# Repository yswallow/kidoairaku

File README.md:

## 輝度哀楽

### 最低限の説明

* Pi PicoもしくはISP1807ピッチ変換基板で動きます
* Pi PicoのGP10/ISP1807のP0.14をHIGHにするとNeoPixelに電源を供給します
* コンスルーは左側に12ピンを、右側に13ピンを、シルクを白く塗っている位置に合わせて使用してください。Pi Picoを使う場合は20ピンも使用可能です。

#### スイッチや1N4148Wダイオードを除いた部品のBOM

| Index | 部品名 | 販売URL |
|----|----|----|
| U1 | Raspberry Pi Pico | https://ssci.to/6900 |
| U1 | ISP1807ピッチ変換基板 | https://ssci.to/6100 |
| U1 | ISP1807ピッチ変換基板(Type-C) | https://ssci.to/6454 |
| F1 | ポリヒューズ 2012 | https://akizukidenshi.com/catalog/g/gP-13955/ |
| Q1 | Pch パワーMOSFET IRLML6402 | https://akizukidenshi.com/catalog/g/gI-02553/ |
| Q51 | Nch MOSFET 2N7002 | https://akizukidenshi.com/catalog/g/gI-04256/ |
| R1,R51 | 10kΩ抵抗3216 | https://akizukidenshi.com/catalog/g/gR-11802/ |

##### 未実装

J1, D51 "Schot", C51, R52 "400k", R53 "100k"

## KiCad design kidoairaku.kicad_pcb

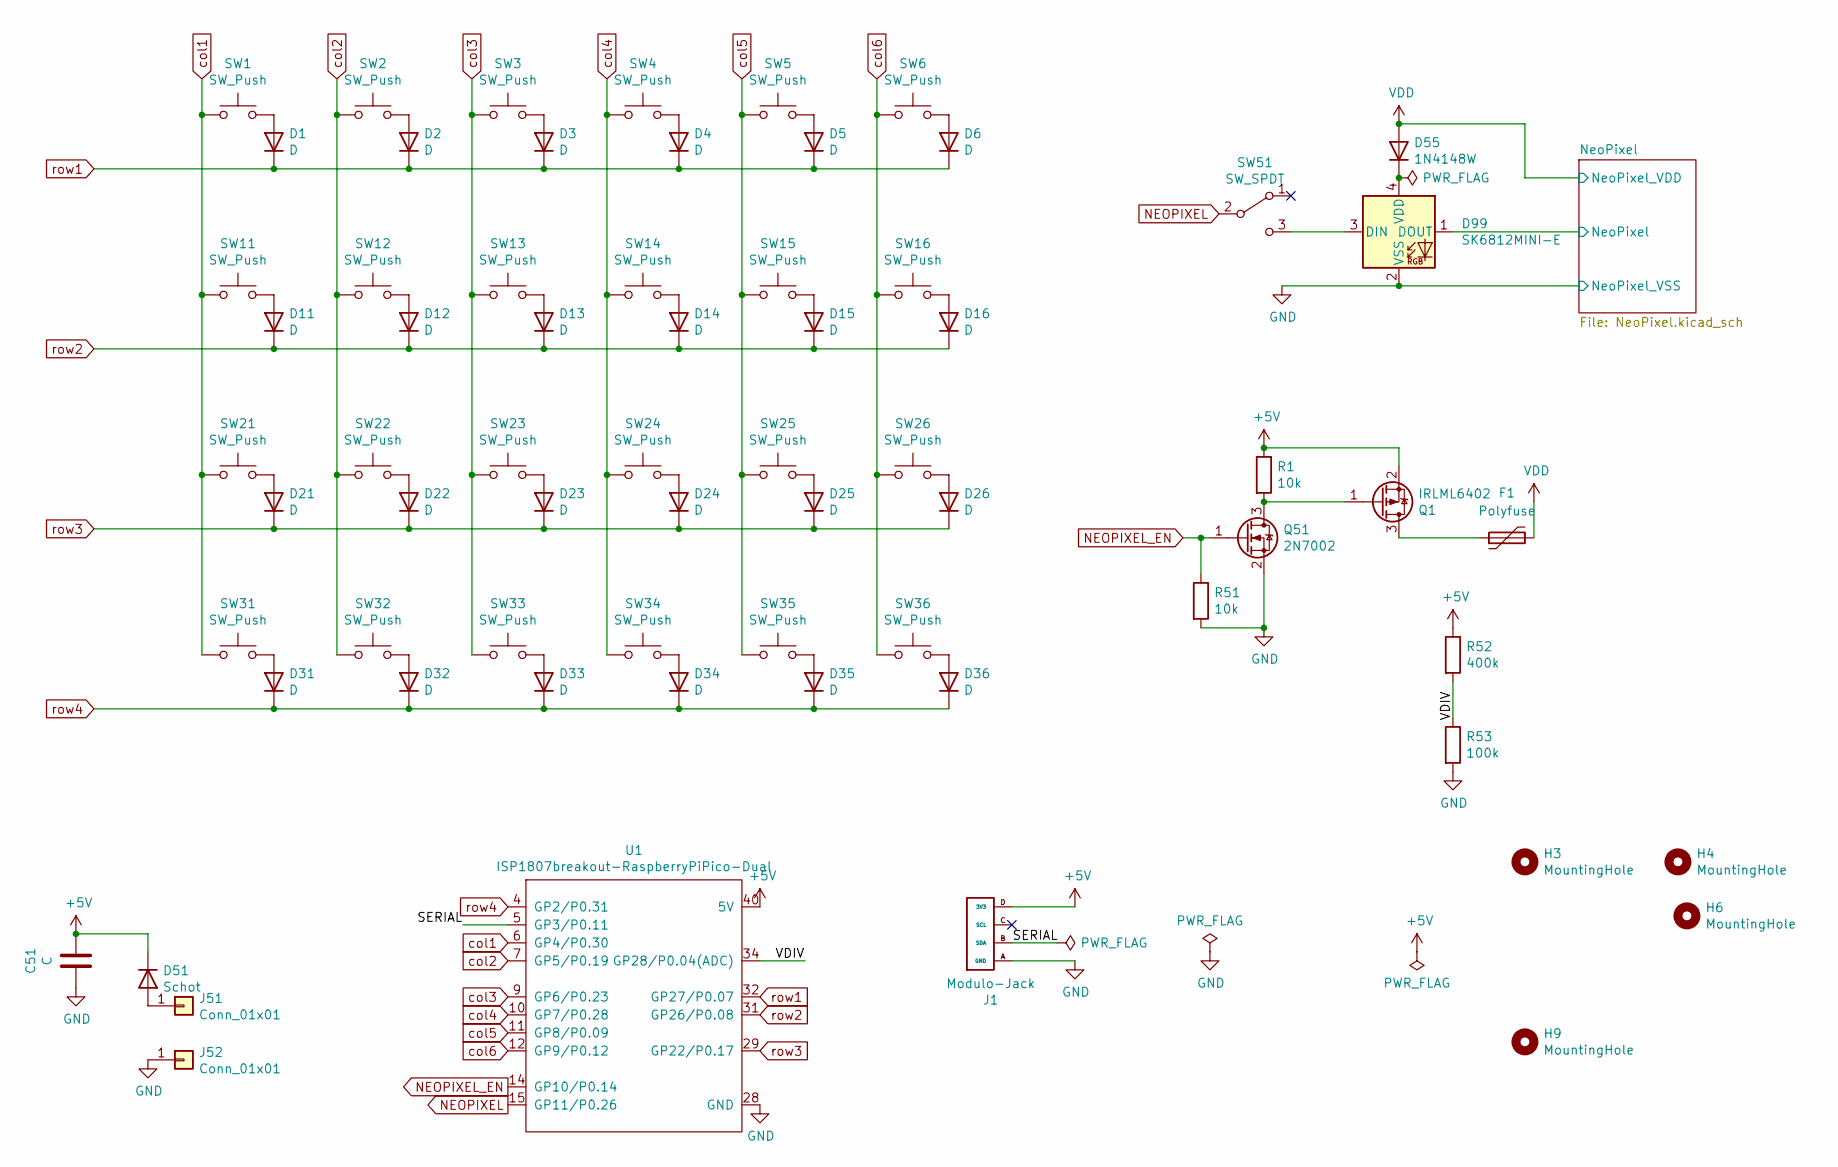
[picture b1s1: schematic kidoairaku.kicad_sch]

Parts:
C51: C; C_1206_3216Metric_Pad1.33x1.80mm_HandSolder
D1, D2, D3, D4, D5, D6, D11, D12, D13, D14, D15, D16, D21, D22, D23, D24, D25, D26, D31, D32, D33, D34, D35, D36: D; D_SOD-123
D51: Schot; D_SOD-123
D55: 1N4148W; D_SOD-123
D99: SK6812MINI-E; SK6812MINI-E_NoSilk-dril
F1: Polyfuse; Fuse_0805_2012Metric_Pad1.15x1.40mm_HandSolder
H3, H4, H6, H9: MountingHole; MountingHole_2.2mm_M2
J1: Modulo-Jack; PJ-320D
J51: Conn_01x01; TestPoint_THTPad_2.0x2.0mm_Drill1.0mm
J52: Conn_01x01; TestPoint_THTPad_D2.0mm_Drill1.0mm
Q1: IRLML6402; SOT-23
Q51: 2N7002; SOT-23
R1, R51: 10k; R_1206_3216Metric_Pad1.30x1.75mm_HandSolder
R52: 400k; R_1206_3216Metric_Pad1.30x1.75mm_HandSolder
R53: 100k; R_1206_3216Metric_Pad1.30x1.75mm_HandSolder
SW1, SW2, SW3, SW4, SW5, SW6, SW11, SW12, SW13, SW14, SW15, SW16, SW21, SW22, SW23, SW24, SW25, SW26, SW31, SW32, SW33, SW34, SW35, SW36: SW_Push; SW_Cherry_MX_1.00u_PCB_Normal
SW51: SW_SPDT; SlideSwitch_SS-12D00
U1: ISP1807breakout-RaspberryPiPico-Dual

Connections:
+5V: C51.1, D51.1 (K), J1.D (3V3), Q1.2 (S), R1.1, R52.1, U1.40 (5V)
/NeoPixel/NeoPixel: D99.1 (DOUT); also elsewhere on the board
/SERIAL: J1.B (SDA), U1.5 (GP3/P0.11)
/VDIV: R52.2, R53.1, U1.34 (GP28/P0.04(ADC))
GND: C51.2, D99.2 (VSS), J1.A (GND), J52.1, Q51.2 (S), R51.2, R53.2, U1.28 (GND); also elsewhere on the board
NEOPIXEL: SW51.2 (B), U1.15 (GP11/P0.26)
NEOPIXEL_EN: Q51.1 (G), R51.1, U1.14 (GP10/P0.14)
unnamed: D1.2 (A), SW1.2
unnamed: D2.2 (A), SW2.2
unnamed: D3.2 (A), SW3.2
unnamed: D4.2 (A), SW4.2
unnamed: D5.2 (A), SW5.2
unnamed: D6.2 (A), SW6.2
unnamed: D11.2 (A), SW11.2
unnamed: D12.2 (A), SW12.2
unnamed: D13.2 (A), SW13.2
unnamed: D14.2 (A), SW14.2
unnamed: D15.2 (A), SW15.2
unnamed: D16.2 (A), SW16.2
unnamed: D21.2 (A), SW21.2
unnamed: D22.2 (A), SW22.2
unnamed: D23.2 (A), SW23.2
unnamed: D24.2 (A), SW24.2
unnamed: D25.2 (A), SW25.2
unnamed: D26.2 (A), SW26.2
unnamed: D31.2 (A), SW31.2
unnamed: D32.2 (A), SW32.2
unnamed: D33.2 (A), SW33.2
unnamed: D34.2 (A), SW34.2
unnamed: D35.2 (A), SW35.2
unnamed: D36.2 (A), SW36.2
unnamed: D51.2 (A), J51.1
unnamed: D55.1 (K), D99.4 (VDD)
unnamed: D99.3 (DIN), SW51.3 (C)
unnamed: F1.1, Q1.3 (D)
unnamed: Q1.1 (G), Q51.3 (D), R1.2
VDD: D55.2 (A), F1.2; also elsewhere on the board
col1: SW1.1, SW11.1, SW21.1, SW31.1, U1.6 (GP4/P0.30)
col2: SW2.1, SW12.1, SW22.1, SW32.1, U1.7 (GP5/P0.19)
col3: SW3.1, SW13.1, SW23.1, SW33.1, U1.9 (GP6/P0.23)
col4: SW4.1, SW14.1, SW24.1, SW34.1, U1.10 (GP7/P0.28)
col5: SW5.1, SW15.1, SW25.1, SW35.1, U1.11 (GP8/P0.09)
col6: SW6.1, SW16.1, SW26.1, SW36.1, U1.12 (GP9/P0.12)
row1: D1.1 (K), D2.1 (K), D3.1 (K), D4.1 (K), D5.1 (K), D6.1 (K), U1.32 (GP27/P0.07)
row2: D11.1 (K), D12.1 (K), D13.1 (K), D14.1 (K), D15.1 (K), D16.1 (K), U1.31 (GP26/P0.08)
row3: D21.1 (K), D22.1 (K), D23.1 (K), D24.1 (K), D25.1 (K), D26.1 (K), U1.29 (GP22/P0.17)
row4: D31.1 (K), D32.1 (K), D33.1 (K), D34.1 (K), D35.1 (K), D36.1 (K), U1.4 (GP2/P0.31)

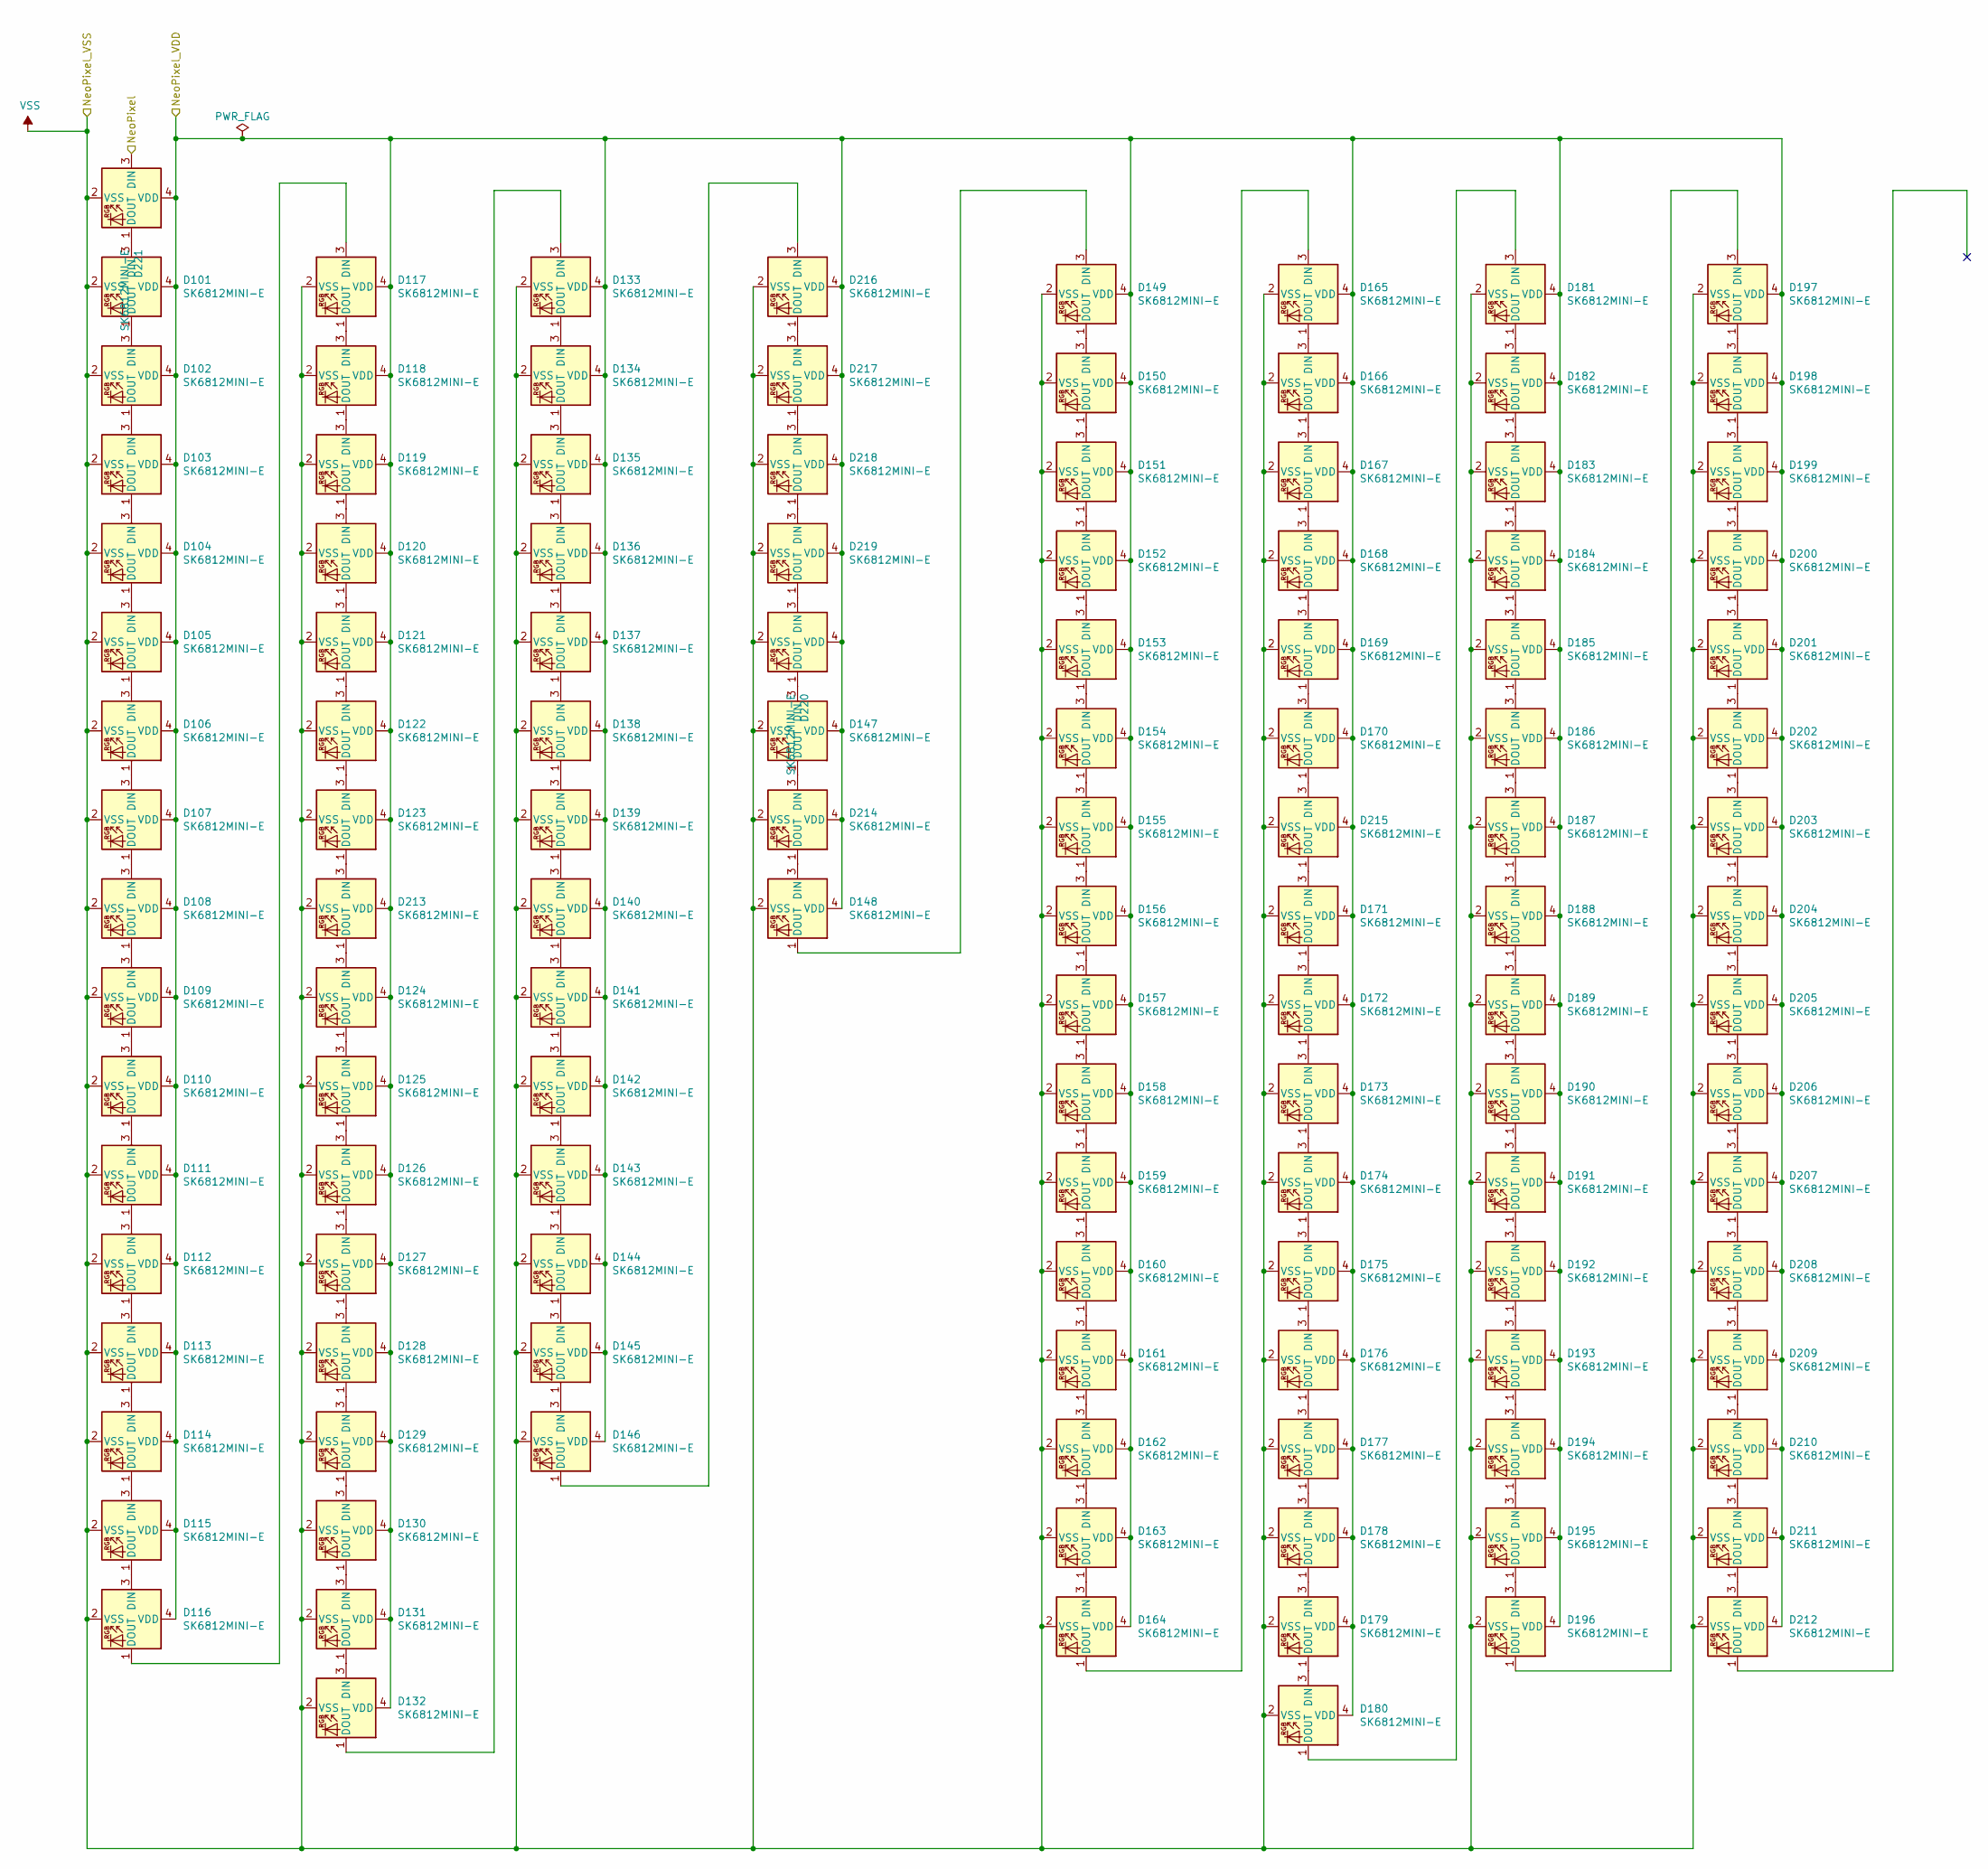
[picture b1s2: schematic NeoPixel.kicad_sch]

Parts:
D101, D102, D103, D104, D105, D106, D107, D108, D109, D110, D111, D112, D113, D114, D115, D116, D117, D118, D119, D120, D121, D122, D123, D124, D125, D126, D127, D128, D129, D130, D131, D132, D133, D134, D135, D136, D137, D138, D139, D140, D141, D142, D143, D144, D145, D146, D147, D148, D149, D150, D151, D152, D153, D154, D155, D156, D157, D158, D159, D160, D161, D162, D163, D164, D165, D166, D167, D168, D169, D170, D171, D172, D173, D174, D175, D176, D177, D178, D179, D180, D181, D182, D183, D184, D185, D186, D187, D188, D189, D190, D191, D192, D213, D214, D215, D216, D217, D218, D219, D220, D221: SK6812MINI-E; SK6812MINI-E_NoSilk-dril
D193, D194, D195, D196, D197, D198, D199, D200, D201, D202, D203, D204, D205, D206, D207, D208, D209, D210, D211, D212: SK6812MINI-E; SK6812MINI-E_NoSilk-dril-front

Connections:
/NeoPixel/NeoPixel: D221.3 (DIN); also elsewhere on the board
GND: D101.2 (VSS), D102.2 (VSS), D103.2 (VSS), D104.2 (VSS), D105.2 (VSS), D106.2 (VSS), D107.2 (VSS), D108.2 (VSS), D109.2 (VSS), D110.2 (VSS), D111.2 (VSS), D112.2 (VSS), D113.2 (VSS), D114.2 (VSS), D115.2 (VSS), D116.2 (VSS), D117.2 (VSS), D118.2 (VSS), D119.2 (VSS), D120.2 (VSS), D121.2 (VSS), D122.2 (VSS), D123.2 (VSS), D124.2 (VSS), D125.2 (VSS), D126.2 (VSS), D127.2 (VSS), D128.2 (VSS), D129.2 (VSS), D130.2 (VSS), D131.2 (VSS), D132.2 (VSS), D133.2 (VSS), D134.2 (VSS), D135.2 (VSS), D136.2 (VSS), D137.2 (VSS), D138.2 (VSS), D139.2 (VSS), D140.2 (VSS), D141.2 (VSS), D142.2 (VSS), D143.2 (VSS), D144.2 (VSS), D145.2 (VSS), D146.2 (VSS), D147.2 (VSS), D148.2 (VSS), D149.2 (VSS), D150.2 (VSS), D151.2 (VSS), D152.2 (VSS), D153.2 (VSS), D154.2 (VSS), D155.2 (VSS), D156.2 (VSS), D157.2 (VSS), D158.2 (VSS), D159.2 (VSS), D160.2 (VSS), D161.2 (VSS), D162.2 (VSS), D163.2 (VSS), D164.2 (VSS), D165.2 (VSS), D166.2 (VSS), D167.2 (VSS), D168.2 (VSS), D169.2 (VSS), D170.2 (VSS), D171.2 (VSS), D172.2 (VSS), D173.2 (VSS), D174.2 (VSS), D175.2 (VSS), D176.2 (VSS), D177.2 (VSS), D178.2 (VSS), D179.2 (VSS), D180.2 (VSS), D181.2 (VSS), D182.2 (VSS), D183.2 (VSS), D184.2 (VSS), D185.2 (VSS), D186.2 (VSS), D187.2 (VSS), D188.2 (VSS), D189.2 (VSS), D190.2 (VSS), D191.2 (VSS), D192.2 (VSS), D193.2 (VSS), D194.2 (VSS), D195.2 (VSS), D196.2 (VSS), D197.2 (VSS), D198.2 (VSS), D199.2 (VSS), D200.2 (VSS), D201.2 (VSS), D202.2 (VSS), D203.2 (VSS), D204.2 (VSS), D205.2 (VSS), D206.2 (VSS), D207.2 (VSS), D208.2 (VSS), D209.2 (VSS), D210.2 (VSS), D211.2 (VSS), D212.2 (VSS), D213.2 (VSS), D214.2 (VSS), D215.2 (VSS), D216.2 (VSS), D217.2 (VSS), D218.2 (VSS), D219.2 (VSS), D220.2 (VSS), D221.2 (VSS); also elsewhere on the board
unnamed: D101.1 (DOUT), D102.3 (DIN)
unnamed: D101.3 (DIN), D221.1 (DOUT)
unnamed: D102.1 (DOUT), D103.3 (DIN)
unnamed: D103.1 (DOUT), D104.3 (DIN)
unnamed: D104.1 (DOUT), D105.3 (DIN)
unnamed: D105.1 (DOUT), D106.3 (DIN)
unnamed: D106.1 (DOUT), D107.3 (DIN)
unnamed: D107.1 (DOUT), D108.3 (DIN)
unnamed: D108.1 (DOUT), D109.3 (DIN)
unnamed: D109.1 (DOUT), D110.3 (DIN)
unnamed: D110.1 (DOUT), D111.3 (DIN)
unnamed: D111.1 (DOUT), D112.3 (DIN)
unnamed: D112.1 (DOUT), D113.3 (DIN)
unnamed: D113.1 (DOUT), D114.3 (DIN)
unnamed: D114.1 (DOUT), D115.3 (DIN)
unnamed: D115.1 (DOUT), D116.3 (DIN)
unnamed: D116.1 (DOUT), D117.3 (DIN)
unnamed: D117.1 (DOUT), D118.3 (DIN)
unnamed: D118.1 (DOUT), D119.3 (DIN)
unnamed: D119.1 (DOUT), D120.3 (DIN)
unnamed: D120.1 (DOUT), D121.3 (DIN)
unnamed: D121.1 (DOUT), D122.3 (DIN)
unnamed: D122.1 (DOUT), D123.3 (DIN)
unnamed: D123.1 (DOUT), D213.3 (DIN)
unnamed: D124.1 (DOUT), D125.3 (DIN)
unnamed: D124.3 (DIN), D213.1 (DOUT)
unnamed: D125.1 (DOUT), D126.3 (DIN)
unnamed: D126.1 (DOUT), D127.3 (DIN)
unnamed: D127.1 (DOUT), D128.3 (DIN)
unnamed: D128.1 (DOUT), D129.3 (DIN)
unnamed: D129.1 (DOUT), D130.3 (DIN)
unnamed: D130.1 (DOUT), D131.3 (DIN)
unnamed: D131.1 (DOUT), D132.3 (DIN)
unnamed: D132.1 (DOUT), D133.3 (DIN)
unnamed: D133.1 (DOUT), D134.3 (DIN)
unnamed: D134.1 (DOUT), D135.3 (DIN)
unnamed: D135.1 (DOUT), D136.3 (DIN)
unnamed: D136.1 (DOUT), D137.3 (DIN)
unnamed: D137.1 (DOUT), D138.3 (DIN)
unnamed: D138.1 (DOUT), D139.3 (DIN)
unnamed: D139.1 (DOUT), D140.3 (DIN)
unnamed: D140.1 (DOUT), D141.3 (DIN)
unnamed: D141.1 (DOUT), D142.3 (DIN)
unnamed: D142.1 (DOUT), D143.3 (DIN)
unnamed: D143.1 (DOUT), D144.3 (DIN)
unnamed: D144.1 (DOUT), D145.3 (DIN)
unnamed: D145.1 (DOUT), D146.3 (DIN)
unnamed: D146.1 (DOUT), D216.3 (DIN)
unnamed: D147.1 (DOUT), D214.3 (DIN)
unnamed: D147.3 (DIN), D220.1 (DOUT)
unnamed: D148.1 (DOUT), D149.3 (DIN)
unnamed: D148.3 (DIN), D214.1 (DOUT)
unnamed: D149.1 (DOUT), D150.3 (DIN)
unnamed: D150.1 (DOUT), D151.3 (DIN)
unnamed: D151.1 (DOUT), D152.3 (DIN)
unnamed: D152.1 (DOUT), D153.3 (DIN)
unnamed: D153.1 (DOUT), D154.3 (DIN)
unnamed: D154.1 (DOUT), D155.3 (DIN)
unnamed: D155.1 (DOUT), D156.3 (DIN)
unnamed: D156.1 (DOUT), D157.3 (DIN)
unnamed: D157.1 (DOUT), D158.3 (DIN)
unnamed: D158.1 (DOUT), D159.3 (DIN)
unnamed: D159.1 (DOUT), D160.3 (DIN)
unnamed: D160.1 (DOUT), D161.3 (DIN)
unnamed: D161.1 (DOUT), D162.3 (DIN)
unnamed: D162.1 (DOUT), D163.3 (DIN)
unnamed: D163.1 (DOUT), D164.3 (DIN)
unnamed: D164.1 (DOUT), D165.3 (DIN)
unnamed: D165.1 (DOUT), D166.3 (DIN)
unnamed: D166.1 (DOUT), D167.3 (DIN)
unnamed: D167.1 (DOUT), D168.3 (DIN)
unnamed: D168.1 (DOUT), D169.3 (DIN)
unnamed: D169.1 (DOUT), D170.3 (DIN)
unnamed: D170.1 (DOUT), D215.3 (DIN)
unnamed: D171.1 (DOUT), D172.3 (DIN)
unnamed: D171.3 (DIN), D215.1 (DOUT)
unnamed: D172.1 (DOUT), D173.3 (DIN)
unnamed: D173.1 (DOUT), D174.3 (DIN)
unnamed: D174.1 (DOUT), D175.3 (DIN)
unnamed: D175.1 (DOUT), D176.3 (DIN)
unnamed: D176.1 (DOUT), D177.3 (DIN)
unnamed: D177.1 (DOUT), D178.3 (DIN)
unnamed: D178.1 (DOUT), D179.3 (DIN)
unnamed: D179.1 (DOUT), D180.3 (DIN)
unnamed: D180.1 (DOUT), D181.3 (DIN)
unnamed: D181.1 (DOUT), D182.3 (DIN)
unnamed: D182.1 (DOUT), D183.3 (DIN)
unnamed: D183.1 (DOUT), D184.3 (DIN)
unnamed: D184.1 (DOUT), D185.3 (DIN)
unnamed: D185.1 (DOUT), D186.3 (DIN)
unnamed: D186.1 (DOUT), D187.3 (DIN)
unnamed: D187.1 (DOUT), D188.3 (DIN)
unnamed: D188.1 (DOUT), D189.3 (DIN)
unnamed: D189.1 (DOUT), D190.3 (DIN)
unnamed: D190.1 (DOUT), D191.3 (DIN)
unnamed: D191.1 (DOUT), D192.3 (DIN)
unnamed: D192.1 (DOUT), D193.3 (DIN)
unnamed: D193.1 (DOUT), D194.3 (DIN)
unnamed: D194.1 (DOUT), D195.3 (DIN)
unnamed: D195.1 (DOUT), D196.3 (DIN)
unnamed: D196.1 (DOUT), D197.3 (DIN)
unnamed: D197.1 (DOUT), D198.3 (DIN)
unnamed: D198.1 (DOUT), D199.3 (DIN)
unnamed: D199.1 (DOUT), D200.3 (DIN)
unnamed: D200.1 (DOUT), D201.3 (DIN)
unnamed: D201.1 (DOUT), D202.3 (DIN)
unnamed: D202.1 (DOUT), D203.3 (DIN)
unnamed: D203.1 (DOUT), D204.3 (DIN)
unnamed: D204.1 (DOUT), D205.3 (DIN)
unnamed: D205.1 (DOUT), D206.3 (DIN)
unnamed: D206.1 (DOUT), D207.3 (DIN)
unnamed: D207.1 (DOUT), D208.3 (DIN)
unnamed: D208.1 (DOUT), D209.3 (DIN)
unnamed: D209.1 (DOUT), D210.3 (DIN)
unnamed: D210.1 (DOUT), D211.3 (DIN)
unnamed: D211.1 (DOUT), D212.3 (DIN)
unnamed: D216.1 (DOUT), D217.3 (DIN)
unnamed: D217.1 (DOUT), D218.3 (DIN)
unnamed: D218.1 (DOUT), D219.3 (DIN)
unnamed: D219.1 (DOUT), D220.3 (DIN)
VDD: D101.4 (VDD), D102.4 (VDD), D103.4 (VDD), D104.4 (VDD), D105.4 (VDD), D106.4 (VDD), D107.4 (VDD), D108.4 (VDD), D109.4 (VDD), D110.4 (VDD), D111.4 (VDD), D112.4 (VDD), D113.4 (VDD), D114.4 (VDD), D115.4 (VDD), D116.4 (VDD), D117.4 (VDD), D118.4 (VDD), D119.4 (VDD), D120.4 (VDD), D121.4 (VDD), D122.4 (VDD), D123.4 (VDD), D124.4 (VDD), D125.4 (VDD), D126.4 (VDD), D127.4 (VDD), D128.4 (VDD), D129.4 (VDD), D130.4 (VDD), D131.4 (VDD), D132.4 (VDD), D133.4 (VDD), D134.4 (VDD), D135.4 (VDD), D136.4 (VDD), D137.4 (VDD), D138.4 (VDD), D139.4 (VDD), D140.4 (VDD), D141.4 (VDD), D142.4 (VDD), D143.4 (VDD), D144.4 (VDD), D145.4 (VDD), D146.4 (VDD), D147.4 (VDD), D148.4 (VDD), D149.4 (VDD), D150.4 (VDD), D151.4 (VDD), D152.4 (VDD), D153.4 (VDD), D154.4 (VDD), D155.4 (VDD), D156.4 (VDD), D157.4 (VDD), D158.4 (VDD), D159.4 (VDD), D160.4 (VDD), D161.4 (VDD), D162.4 (VDD), D163.4 (VDD), D164.4 (VDD), D165.4 (VDD), D166.4 (VDD), D167.4 (VDD), D168.4 (VDD), D169.4 (VDD), D170.4 (VDD), D171.4 (VDD), D172.4 (VDD), D173.4 (VDD), D174.4 (VDD), D175.4 (VDD), D176.4 (VDD), D177.4 (VDD), D178.4 (VDD), D179.4 (VDD), D180.4 (VDD), D181.4 (VDD), D182.4 (VDD), D183.4 (VDD), D184.4 (VDD), D185.4 (VDD), D186.4 (VDD), D187.4 (VDD), D188.4 (VDD), D189.4 (VDD), D190.4 (VDD), D191.4 (VDD), D192.4 (VDD), D193.4 (VDD), D194.4 (VDD), D195.4 (VDD), D196.4 (VDD), D197.4 (VDD), D198.4 (VDD), D199.4 (VDD), D200.4 (VDD), D201.4 (VDD), D202.4 (VDD), D203.4 (VDD), D204.4 (VDD), D205.4 (VDD), D206.4 (VDD), D207.4 (VDD), D208.4 (VDD), D209.4 (VDD), D210.4 (VDD), D211.4 (VDD), D212.4 (VDD), D213.4 (VDD), D214.4 (VDD), D215.4 (VDD), D216.4 (VDD), D217.4 (VDD), D218.4 (VDD), D219.4 (VDD), D220.4 (VDD), D221.4 (VDD); also elsewhere on the board

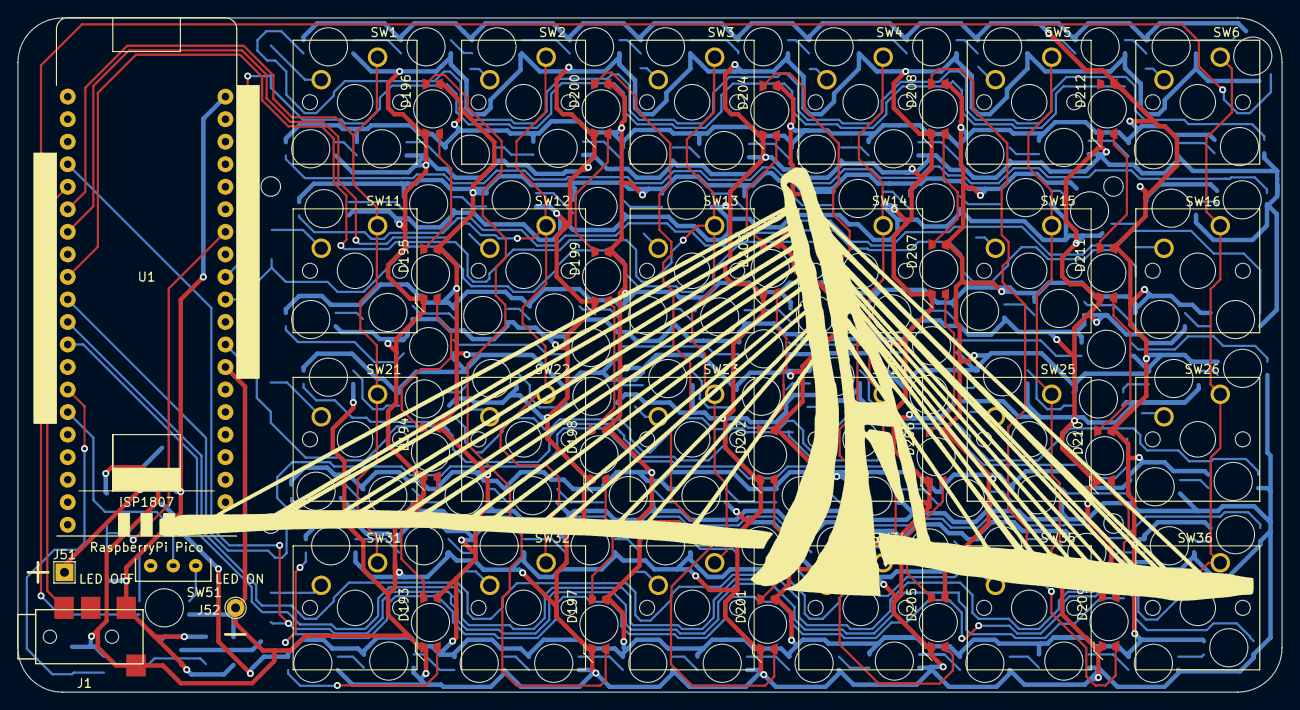
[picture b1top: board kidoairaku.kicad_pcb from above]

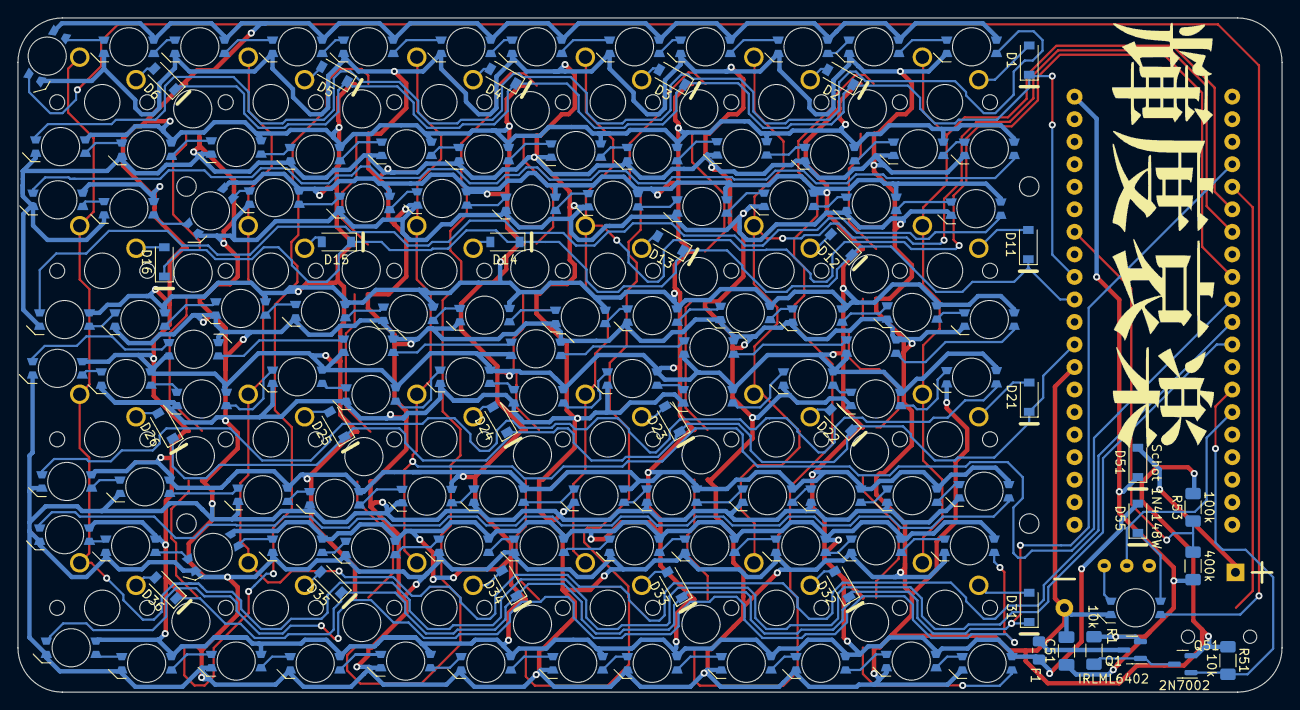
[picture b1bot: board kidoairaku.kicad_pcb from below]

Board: 2 copper layers, 142.5 x 76.0 mm, 189 parts (34 on the bottom side), 167 nets.

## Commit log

2022-02-20 init
2022-03-31 first production
2022-03-31 add buildguide
2022-09-02 Create LICENSE
